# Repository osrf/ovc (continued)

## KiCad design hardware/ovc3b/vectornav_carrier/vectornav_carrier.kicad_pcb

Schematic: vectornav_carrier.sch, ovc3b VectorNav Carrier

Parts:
C14, C16, C21, C24, C25: 100n; C_0603_1608Metric; MPN CL10B104KO8NNNC
C20, C22: 47p; C_0603_1608Metric; MPN GCM1885C2A470JA16D
C23: 10u; C_0603_1608Metric; MPN GRM188R61A106KE69D
D1: RXLED; LED_0603_1608Metric; MPN LTST-C191KRKT
D2: TXLED; LED_0603_1608Metric; MPN LTST-C191KGKT
FB1: ferrite; R_0603_1608Metric; MPN BLM18KG601SN1D
H1, H2, H3, H4: MountingHole_Pad; MountingHole_2.2mm_M2_Pad
J1: camera; PinSocket_2x08_P2.00mm_Vertical
J2: Xilinx programmer; PinHeader_2x07_P2.00mm_Vertical_SMD; MPN 0878321420
J3: ROOT CONSOLE; PinHeader_1x03_P2.54mm_Vertical; MPN DNP
J4: VECTORNAV_UART; PinHeader_1x03_P2.54mm_Vertical; MPN DNP
J5: USB_B_Micro; USB_Micro-B_Wuerth_629105150521_CircularHoles; MPN 629105150521
R1, R2: 27R; R_0603_1608Metric; MPN RC0603FR-0727RL
R3, R4: 270R; R_0603_1608Metric; MPN RC0603FR-07270RL
U1: VN-100; MPN DNP
U5: SN74AXCH8T245; TSSOP-24_4.4x7.8mm_P0.65mm; MPN SN74AXCH8T245PWR
U8: FT230XS; SSOP-16_3.9x4.9mm_P0.635mm; MPN FT230XS-R

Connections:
+1V2: C14.1, J1.4, U5.1 (VCCA), U5.2 (DIR1), U5.11 (DIR2)
/AUX0_1V2: J1.3, U5.8 (A6)
/AUX1_1V2: J1.5, U5.5 (A3)
/AUX2_1V2: J1.7, U5.4 (A2)
/AUX3_1V2: J1.9, U5.3 (A1)
/AUX4_1V2: J1.11, U5.7 (A5)
/AUX5_1V2: J1.6, U5.6 (A4)
/IMU_CS: U1.23 (SPI_CS#), U5.18 (B4)
/IMU_MISO: U1.19 (SPI_MISO), U5.16 (B6)
/IMU_MOSI: U1.17 (SPI_MOSI), U5.20 (B2)
/IMU_NRST: U1.21 (NRST), U5.19 (B3)
/IMU_RX1: J4.2, U1.13 (RX1)
/IMU_RX2: U1.6 (RX2)
/IMU_SCK: U1.16 (SPI_SCK), U5.21 (B1)
/IMU_SYNC_OUT: U1.9 (SYNC_OUT), U5.17 (B5)
/IMU_TX1: J4.3, U1.12 (TX1)
/IMU_TX2: U1.5 (TX2)
/JTAG_TCK: J1.14, J2.6
/JTAG_TDI: J1.12, J2.10
/JTAG_TDO: J1.13, J2.8
/JTAG_TMS: J1.15, J2.4
/ROOT_RX: J1.10, J3.2, U8.1 (TXD)
/ROOT_TX: J1.8, J3.3, U8.4 (RXD)
/RXLED: R3.2, U8.14 (CBUS1)
/TXLED: R4.2, U8.7 (CBUS2)
/USB_3V3: C25.1, D1.2 (A), D2.2 (A), U8.3 (VCCIO), U8.10 (3V3OUT), U8.11 (~RESET)
/USB_D+: R1.1, U8.8 (USBDP)
/USB_D-: R2.1, U8.9 (USBDM)
/USB_VCC: C23.1, C24.1, FB1.1, U8.12 (VCC)
/VCC_JTAG: J1.16, J2.2
GND: C14.2, C16.2, C20.2, C21.2, C22.2, C23.2, C24.2, C25.2, H1.1, H2.1, H3.1, H4.1, J1.2, J2.3, J2.5, J2.7, J2.9, J2.11, J2.13, J3.1, J4.1, J5.5 (GND), U1.1 (GND), U1.2 (GND), U1.3 (GND), U1.4 (GND), U1.18 (GND), U1.28 (GND), U1.30 (GND), U5.12 (GND), U5.13 (GND), U5.14 (B8), U5.15 (B7), U5.22 (~OE), U8.5 (GND), U8.13 (GND)
unnamed: C20.1, J5.3 (D+), R1.2
unnamed: C21.1, FB1.2, J5.1 (VBUS)
unnamed: C22.1, J5.2 (D-), R2.2
unnamed: D1.1 (K), R3.1
unnamed: D2.1 (K), R4.1

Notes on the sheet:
VN-100
always enabled 1:4 A->B 5:8 B->A
INPUT
OUTPUT
USB-UART for linux root console

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
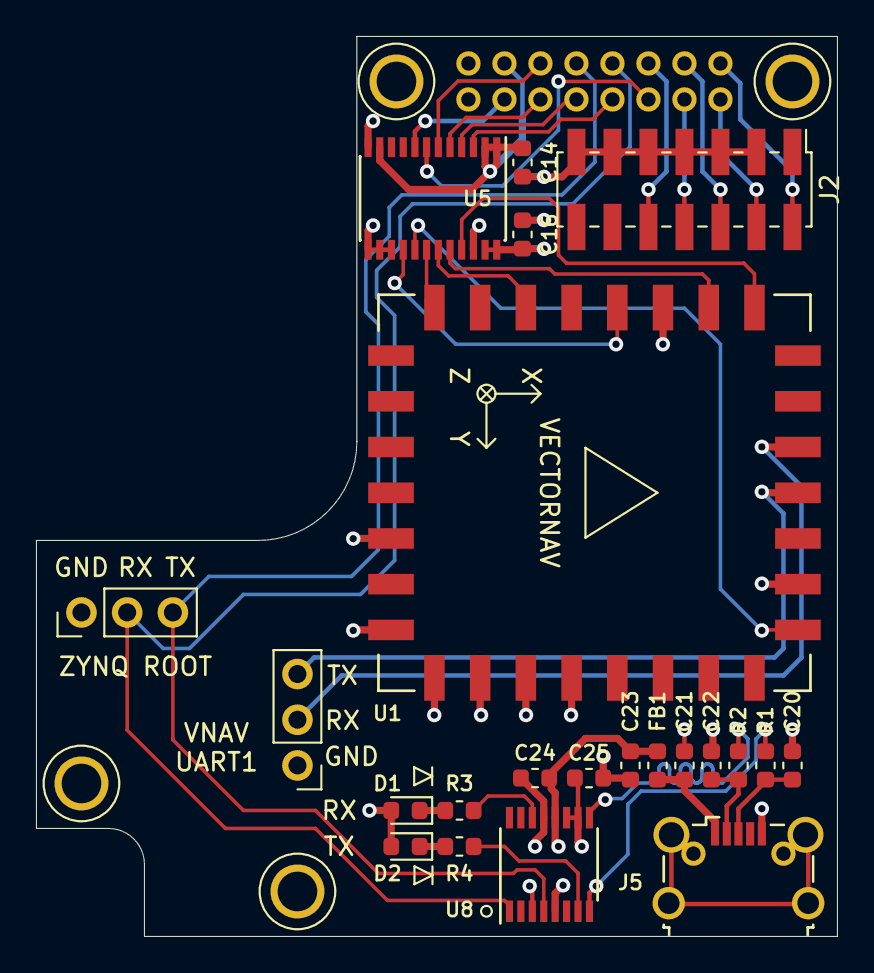
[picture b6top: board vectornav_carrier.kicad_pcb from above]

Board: 4 copper layers, 44.5 x 50.0 mm, 27 parts (1 on the bottom side), 35 nets.

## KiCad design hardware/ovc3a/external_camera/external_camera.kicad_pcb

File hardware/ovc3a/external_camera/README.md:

# Lens holders
Lens holders have 20mm spacing. There are various options that work fine.
We have used PT-LH010M from m12lenses.com with good results:
https://www.m12lenses.com/CNC-Machined-M12-Lens-Holder-Metal-p/pt-lh010m.htm

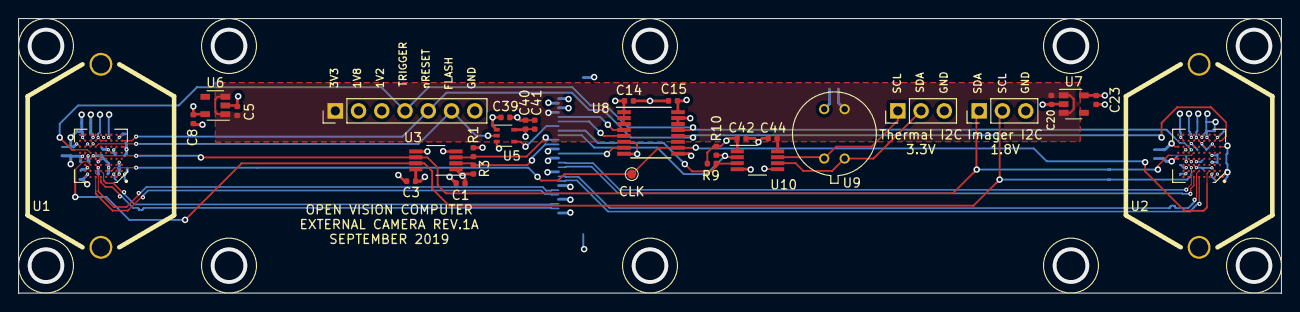
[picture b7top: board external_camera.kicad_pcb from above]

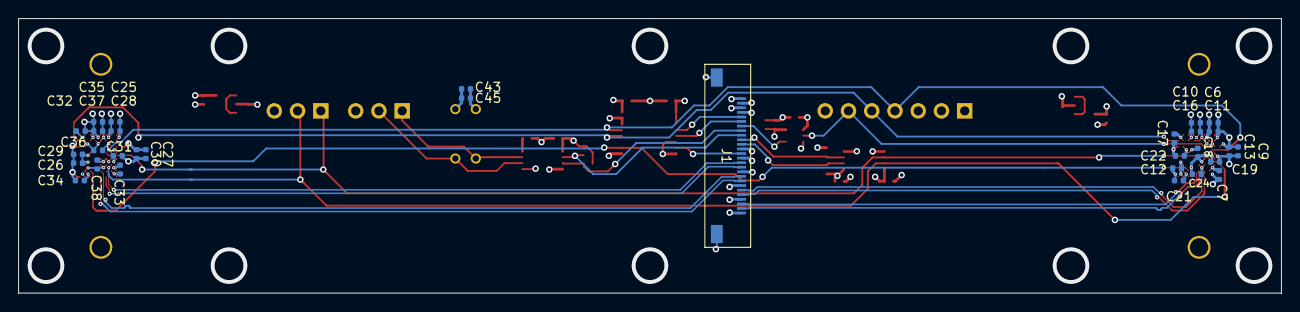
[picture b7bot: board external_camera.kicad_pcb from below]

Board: 6 copper layers, 138.0 x 30.0 mm, 63 parts (31 on the bottom side), 30 nets.

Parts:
C1, C3, C11, C12, C13, C14, C15, C16, C17, C18, C19, C21, C22, C24, C28, C29, C30, C32, C33, C34, C35, C36, C37, C38, C39, C40, C42, C43, C44: 100n; C_0402_1005Metric
C5, C8, C20, C23, C45: 1u; C_0402_1005Metric
C6, C7, C9, C10, C25, C26, C27, C31, C41: 10u; C_0402_1005Metric
J1: FFC; MOLEX_505110_2691
J2, J3: DNP; LENS_HOLDER_20MM_PT-LH010M
J4: DNP; PinHeader_1x07_P2.54mm_Vertical
J5, J6: DNP; PinHeader_1x03_P2.54mm_Vertical
R1, R3: 2k2; R_0402_1005Metric
R9, R10: DNP; R_0402_1005Metric
TP1: DNP; TestPoint_Pad_D1.0mm
U1, U2: AR0144CS; BGA-72_9x8_5.545x5.565mm
U3, U10: TCA9803; VSSOP-8_3.0x3.0mm_P0.65mm
U5: SN74AUP1T34DCK; SOT-353_SC-70-5
U6, U7: LP5907MFX-2.8; SOT-23-5
U8: SN74AXC4T245PWR; TSSOP-16_4.4x5mm_P0.65mm
U9: DNP; Melexis_TO-39

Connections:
+1V2: C1.1, C10.1, C14.1, C16.1, C19.1, C21.1, C22.1, C24.1, C31.1, C34.1, C35.1, C36.1, C37.1, C38.1, C40.1, C41.1, C42.1, J1.2, J4.3, R1.1, R3.1, R9.1, R10.1, U1.A3, U1.B2, U1.C5, U1.C6, U1.D8, U1.F2, U1.G4, U1.G5, U1.G6, U2.A3, U2.B2, U2.C5, U2.C6, U2.D8, U2.F2, U2.G4, U2.G5, U2.G6, U3.1, U3.5, U5.5, U8.1, U8.2, U8.3, U10.1, U10.5
+1V8: C3.1, C7.1, C12.1, C15.1, C18.1, C26.1, C29.1, C33.1, C39.1, J1.3, J4.2, U1.A2, U1.B7, U1.B8, U1.C2, U1.C8, U1.E3, U2.A2, U2.B8, U2.C2, U2.C8, U2.E3, U3.8, U5.1, U8.16
+3V3: C5.1, C20.1, C43.1, C44.1, C45.1, J1.4, J4.1, U6.1, U6.3, U7.1, U7.3, U9.2, U10.8
/CAM0_2V8: C6.1, C8.1, C9.1, C11.1, C13.1, C17.1, U1.F9, U1.G2, U1.G8, U1.H1, U1.H2, U1.H8, U1.H9, U6.5
/CAM1_2V8: C23.1, C25.1, C27.1, C28.1, C30.1, C32.1, U2.F9, U2.G2, U2.G8, U2.H1, U2.H2, U2.H8, U2.H9, U7.5
/EXTCLK_1V2: J1.13, U8.7
/EXTCLK_1V8: TP1.1, U1.B3, U2.B3, U8.10
/FLASH_1V2: J1.7, U5.4
/FLASH_1V8: J4.6, U1.F6, U5.2
/MIPI_CLK0+: J1.25, U1.A5
/MIPI_CLK0-: J1.24, U1.B5
/MIPI_CLK1+: J1.19, U2.A5
/MIPI_CLK1-: J1.18, U2.B5
/MIPI_DAT0+: J1.22, U1.A6
/MIPI_DAT0-: J1.21, U1.B6
/MIPI_DAT1+: J1.16, U2.A6
/MIPI_DAT1-: J1.15, U2.B6
/RESET_1V2: J1.6, U8.5
/RESET_1V8: J4.5, U1.G1, U2.G1, U8.12
/SCL0_1V2: J1.11, R3.2, U3.2
/SCL0_1V8: J5.2, U1.C7, U2.C7, U3.7
/SCL1_1V2: J1.9, R10.2, U10.2
/SCL1_3V3: J6.1, U9.4, U10.7
/SDA0_1V2: J1.10, R1.2, U3.3
/SDA0_1V8: J5.1, U1.E6, U2.E6, U3.6
/SDA1_1V2: J1.8, R9.2, U10.3
/SDA1_3V3: J6.2, U9.1, U10.6
/TRIGGER_1V2: J1.5, U8.4
/TRIGGER_1V8: J4.4, U1.E7, U2.E7, U8.13
GND: C1.2, C3.2, C5.2, C6.2, C7.2, C8.2, C9.2, C10.2, C11.2, C12.2, C13.2, C14.2, C15.2, C16.2, C17.2, C18.2, C19.2, C20.2, C21.2, C22.2, C23.2, C24.2, C25.2, C26.2, C27.2, C28.2, C29.2, C30.2, C31.2, C32.2, C33.2, C34.2, C35.2, C36.2, C37.2, C38.2, C39.2, C40.2, C41.2, C42.2, C43.2, C44.2, C45.2, J1.1, J1.12, J1.14, J1.17, J1.20, J1.23, J1.26, J1.27, J2.1, J3.1, J4.7, J5.3, J6.3, U1.A1, U1.A8, U1.D5, U1.D6, U1.D7, U1.D9, U1.E8, U1.F1, U1.F7, U1.F8, U1.G3, U1.G7, U1.H3, U1.H4, U1.H5, U1.H6, U1.H7, U2.A1, U2.A8, U2.B7, U2.D5, U2.D6, U2.D7, U2.D9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

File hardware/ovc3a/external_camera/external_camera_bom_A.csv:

Component,Quantity Per PCB,References,Value,Footprint,MFN,MPN,D1N,D1PN
1,29,C1 C3 C11 C12 C13 C14 C15 C16 C17 C18 C19 C21 C22 C24 C28 C29 C30 C32 C33 C34 C35 C36 C37 C38 C39 C40 C42 C43 C44,100n,C_0402_1005Metric,Samsung,CL05F104ZO5NNNC,Digikey,1276-1004-1-ND
2,9,C6 C7 C9 C10 C25 C26 C27 C31 C41,10u,C_0402_1005Metric,Samsung,CL05A106MP8NUB8,Digikey,1276-6830-1-ND
3,5,C5 C8 C20 C23 C45,1u,C_0402_1005Metric,Samsung,CL05A105KA5NQNC,Digikey,1276-1445-1-ND
4,2 (DNF),J2 J3,DNP,LENS_HOLDER_20MM_PT-LH010M,DNP,DNP,DNP,DNP
5,1 (DNF),J4,DNP,PinHeader_1x07_P2.54mm_Vertical,DNP,DNP,DNP,DNP
6,2 (DNF),J5 J6,DNP,PinHeader_1x03_P2.54mm_Vertical,DNP,DNP,DNP,DNP
7,1,J1,FFC,MOLEX_505110_2691,Molex,5051102691,Digikey,WM24281CT-ND
8,4,R1 R3 R9 R10,2k2,R_0402_1005Metric,Yageo,RC0402FR-072K2L,Digikey,311-2.20KLRCT-ND
9,2,U1 U2,AR0144CS,BGA-72_9x8_5.545x5.565mm,ON Semiconductor,AR0144CSSC00SUKA0-CPBR2,Digikey,AR0144CSSC00SUKA0-CPBR2OS-ND
10,1 (DNF),U9,DNP,Melexis_TO-39,DNP,DNP,DNP,DNP
11,2,U6 U7,LP5907MFX-2.8,SOT-23-5,Texas Instruments,LP5907MFX-2.8/NOPB,Digikey,296-39063-1-ND
12,1,U5,SN74AUP1T34DCK,SOT-353_SC-70-5,Texas Instruments,SN74AUP1T34DCKR,Digikey,296-34900-1-ND
13,1,U8,SN74AXC4T245PWR,TSSOP-16_4.4x5mm_P0.65mm,Texas Instruments,SN74AXC4T245PWR,Digikey,296-53472-1-ND
14,2,U3 U10,TCA9803,VSSOP-8_3.0x3.0mm_P0.65mm,Texas Instruments,TCA9803DGKR,Digikey,296-47829-1-ND





Component Groups:,14
Component Count:,62
Fitted Components:,56
Number of PCBs:,1
Total components:,56
Schematic Version:,A
Schematic Date:,2019-07-10
PCB Variant:,['default']
BoM Date:,Mon 23 Sep 2019 04:11:05 PM +08
Schematic Source:,/home/luca/hw/ovc/hardware/ovc3a/external_camera/external_camera.sch
KiCad Version:,Eeschema 5.99.0-unknown-bba949c~100~ubuntu18.04.1

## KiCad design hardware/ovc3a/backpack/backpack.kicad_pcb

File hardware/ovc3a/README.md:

# ovc3 early design concept

The idea for OVC3 is to dramatically reduce costs from OVC2 by using a
mass-produced high-density module for the FPGA/SoC, RAM, and so on. Ideally
this module will contain a Zynq UltraScale+ SoC with I/O that can function as a
USB3 transceiver.

Some candidate modules:
 * Trenz TE0820 (40mm x 50mm)
 * Trenz TE0803 / TE0808 (52mm x 76mm)
 * UltraZed
 * Enclustra Mercury

# Board Stack

For the smallest front cross-sectional area, it would be necessary to keep
the "sensor" and "compute" portions on separate boards. Unfortunately, this
would also increase small-quantity production costs.

Placing the compute module on the sensor board would make it larger/uglier,
but also keep costs down.

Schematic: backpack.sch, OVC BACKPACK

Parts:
C1, C4, C5, C8, C23: 10u; C_0603_1608Metric
C2, C3, C6, C7, C9, C10, C11, C12, C13, C14, C15, C16, C17, C18, C19, C21, C24, C25, C26: 100n; C_0603_1608Metric
C20, C22: 47p; C_0603_1608Metric
D1: RXLED; LED_0603_1608Metric
D2: TXLED; LED_0603_1608Metric
FB1, FB2: ferrite; R_0603_1608Metric
H1, H2, H3, H4, H5, H6, H7, H8: MountingHole_Pad; MountingHole_3.2mm_M3_DIN965_Pad
J1: GPIO1; Molex_Nano-Fit_105313-xx05_1x05_P2.50mm_Horizontal
J2: TO_CAMERA; PinHeader_2x15_P1.27mm_Vertical
J3: ROOT CONSOLE; PinHeader_1x03_P2.54mm_Vertical
J4: RS232; Molex_Nano-Fit_105313-xx03_1x03_P2.50mm_Horizontal
J5: USB_B_Micro; USB_Micro-B_Wuerth_629105150521_CircularHoles
J6: IMU_UART2; PinHeader_1x03_P2.54mm_Vertical
J7: IMU_UART0; PinHeader_1x03_P2.54mm_Vertical
J8: debug; PinHeader_2x05_P2.54mm_Vertical
J9: debug; PinHeader_1x03_P2.54mm_Vertical
R1, R2: 27R; R_0603_1608Metric
R3, R4: 270R; R_0603_1608Metric
R5, R6: 10k; R_0603_1608Metric
U1: VN-100
U2, U3: ISOW7842; SOIC-16W_7.5x10.3mm_P1.27mm
U4: MAX3221E; TSSOP-16_4.4x5mm_P0.65mm
U5, U6: SN74AXCH8T245; TSSOP-24_4.4x7.8mm_P0.65mm
U7: SN74AVCH2T45; VSSOP-8_2.3x2mm_P0.5mm
U8: FT230XS; SSOP-16_3.9x4.9mm_P0.635mm
U9: uIMU-2

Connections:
+1V2: J2.11, J2.13
+1V8: C14.1, C15.1, C18.1, J2.1, J2.2, U5.1 (VCCA), U5.2 (DIR1), U5.11 (DIR2), U6.1 (VCCA), U6.2 (DIR1), U6.11 (DIR2), U7.1, U7.5
/BONUS_INPUT: J8.3, U6.16 (B6)
/GPIO0_1V8: J2.4, U5.10 (A8)
/GPIO1A: U2.3 (INA), U5.19 (B3)
/GPIO1A_ISO: J1.1, U2.14 (OUTA)
/GPIO1B: U2.4 (INB), U5.18 (B4)
/GPIO1B_ISO: J1.2, U2.13 (OUTB)
/GPIO1C: U2.5 (OUTC), U5.17 (B5)
/GPIO1C_ISO: J1.3, R5.1, U2.12 (INC)
/GPIO1D: U2.6 (OUTD), U5.16 (B6)
/GPIO1D_ISO: J1.4, R6.1, U2.11 (IND)
/GPIO1_1V8: J2.6, U5.9 (A7)
/GPIO1_GND_ISO: C3.2, C4.2, J1.5, R5.2, R6.2, U2.9 (GND2), U2.10 (EN2), U2.15 (GND2)
/GPIO1_VCC_ISO: C3.1, C4.1, U2.16 (VCC2)
/GPIO2_1V8: J2.8, U5.8 (A6)
/GPIO3_1V8: J2.10, U5.7 (A5)
/GPIO4_1V8: J2.12, U5.6 (A4)
/GPIO5_1V8: J2.14, U5.5 (A3)
/GPIO6_1V8: J2.16, U5.4 (A2)
/GPIO7_1V8: J2.18, U5.3 (A1)
/GPIO8_1V8: J2.21, U6.3 (A1)
/GPIO9_1V8: J2.23, U6.4 (A2)
/GPIO10_1V8: J2.25, U6.5 (A3)
/GPIO11_1V8: J2.27, U6.6 (A4)
/GPIO12_1V8: J2.26, U6.7 (A5)
/GPIO13_1V8: J2.24, U6.8 (A6)
/GPIO14_1V8: J2.22, U6.9 (A7)
/GPIO15_1V8: J2.20, U6.10 (A8)
/GPIO16_1V8: J2.17, U7.2
/GPIO17_1V8: J2.19, U7.3
/IMU_CS: J9.2, U1.23 (SPI_CS#), U7.6, U9.8
/IMU_MISO: J8.4, U1.19 (SPI_MISO), U6.15 (B7), U9.7
/IMU_MOSI: J8.7, U1.17 (SPI_MOSI), U6.20 (B2), U9.6
/IMU_NRST: J8.10, U1.21 (NRST), U6.21 (B1), U9.12
/IMU_RX0: J7.2, U9.18
/IMU_RX1: J8.5, U1.13 (RX1), U6.18 (B4)
/IMU_RX2: J6.2, U1.6 (RX2)
/IMU_SCK: J8.8, U1.16 (SPI_SCK), U6.19 (B3), U9.9
/IMU_SYNC_IN: J9.1, U1.22 (SYNC_IN), U7.7, U9.5
/IMU_SYNC_OUT: J8.2, U1.9 (SYNC_OUT), U6.14 (B8), U9.20
/IMU_TX0: J7.1, U9.19
/IMU_TX1: J8.6, U1.12 (TX1), U6.17 (B5)
/IMU_TX2: J6.1, U1.5 (TX2)
/ISO_GND_RS232: C7.2, C8.2, C11.2, C12.1, C13.1, J4.3, U3.9 (GND2), U3.10 (EN2), U3.15 (GND2), U4.1 (~EN), U4.14 (GND)
/ISO_RS232_DIN: U3.14 (OUTA), U4.11 (DIN)
/ISO_RS232_DOUT: J4.1, U4.13 (DOUT)
/ISO_RS232_FORCEON: U3.13 (OUTB), U4.12 (FORCEON)
/ISO_RS232_INVALID: U3.11 (IND), U4.10 (~INVALID)
/ISO_RS232_RIN: J4.2, U4.8 (RIN)
/ISO_RS232_ROUT: U3.12 (INC), U4.9 (ROUT)
/ISO_VCC_RS232: C7.1, C8.1, C11.1, U3.16 (VCC2), U4.15 (VCC), U4.16 (~FORCEOFF)
/ROOT_RX: J2.28, J3.1, U8.1
/ROOT_TX: J2.30, J3.2, U8.4
/RS232_DIN: U3.3 (INA), U5.21 (B1)
/RS232_FORCEON: U3.4 (INB), U5.20 (B2)
/RS232_INVALID: U3.6 (OUTD), U5.14 (B8)
/RS232_ROUT: U3.5 (OUTC), U5.15 (B7)
/RXLED: R3.2, U8.14
/TXLED: R4.2, U8.7
/USB_3V3: C25.1, D1.2, D2.2, U8.3, U8.10, U8.11
/USB_DM: R2.1, U8.9
/USB_DP: R1.1, U8.8
/USB_VCC: C23.1, C24.1, FB1.1, U8.12
GND: C1.2, C2.2, C5.2, C6.2, C14.2, C15.2, C16.2, C17.2, C18.2, C19.2, C20.2, C21.2, C22.2, C23.2, C24.2, C25.2, C26.2, J2.3, J2.9, J2.15, J2.29, J3.3, J5.5, J6.3, J7.3, J8.9, J9.3, U1.1 (GND), U1.2 (GND), U1.3 (GND), U1.4 (GND), U1.18 (GND), U1.28 (GND), U1.30 (GND), U2.2 (GND1), U2.8 (GND1), U3.2 (GND1), U3.8 (GND1), U5.12 (GND), U5.13 (GND), U5.22 (~OE), U6.12 (GND), U6.13 (GND), U6.22 (~OE), U7.4, U8.5, U8.13, U9.10, U9.11, U9.21
unnamed: C9.1, U4.2 (C1+)
unnamed: C9.2, U4.4 (C1-)
unnamed: C10.1, U4.5 (C2+)
unnamed: C10.2, U4.6 (C2-)
unnamed: C12.2, U4.3 (V+)
unnamed: C13.2, U4.7 (V-)
unnamed: C20.1, J5.3, R1.2
unnamed: C21.1, FB1.2, J5.1
unnamed: C22.1, J5.2, R2.2
unnamed: C26.1, FB2.2, U9.3, U9.22
unnamed: D1.1, R3.1
unnamed: D2.1, R4.1

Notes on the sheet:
MOUNTING HOLES
TRENZ MOUNTING HOLES
V_ISO set to 3v3
Isolator for RS-232
always enabled 1:4 A->B 5:8 B->A
Isolator for GPIO
RS-232
VN-100
OUTPUT
INPUT
A->B
InertialSense uIMU family
USB-UART for linux root console
input pulldowns

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
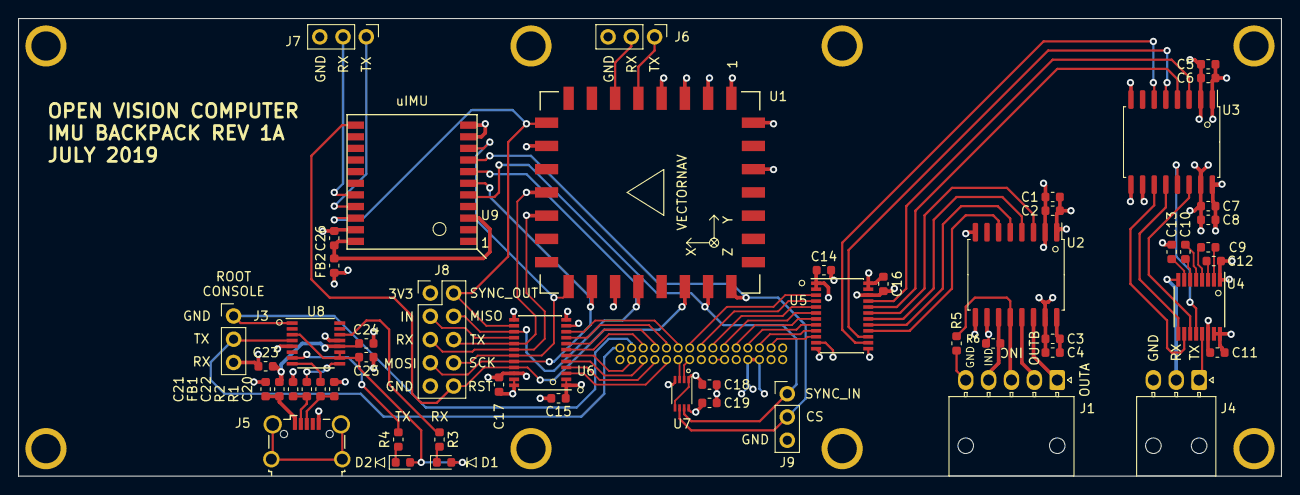
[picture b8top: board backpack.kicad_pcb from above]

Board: 4 copper layers, 138.0 x 50.0 mm, 62 parts (1 on the bottom side), 78 nets.

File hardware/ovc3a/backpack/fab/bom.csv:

# Bill of Materials for 'OVC BACKPACK' rev.A
# Schematic date: Mon Jul  8 23:24:45 2019
Line Item,Quantity,Designator,Footprint,Value,Manufacturer,Manufacturer Part Number
1,5,"C1,C4,C5,C8,C23",Capacitor_SMD:C_0603_1608Metric,10u,Murata,GRM188R61A106KE69D
2,19,"C2,C3,C6,C7,C9,C10,C11,C12,C13,C14,C15,C16,C17,C18,C19,C21,C24,C25,C26",Capacitor_SMD:C_0603_1608Metric,100n,Samsung,CL10B104KO8NNNC
3,2,"C20,C22",Capacitor_SMD:C_0603_1608Metric,47p,Murata,GCM1885C2A470JA16D
4,1,"D1",LED_SMD:LED_0603_1608Metric,RXLED,Lite-On,LTST-C191KRKT
5,1,"D2",LED_SMD:LED_0603_1608Metric,TXLED,Lite-On,LTST-C191KGKT
6,2,"FB1,FB2",Resistor_SMD:R_0603_1608Metric,ferrite,Murata,BLM18KG601SN1D
7,1,"J1",Connector_Molex:Molex_Nano-Fit_105313-xx05_1x05_P2.50mm_Horizontal,GPIO1,Molex,WM15144-ND
8,1,"J2",Connector_PinHeader_1.27mm:PinHeader_2x15_P1.27mm_Vertical,TO_CAMERA,Amphenol/FCI,20021111-00030T4LF
9,5,"J3,J6,J7,J8,J9",DNP,DNP,DNP,DNP
10,1,"J4",Connector_Molex:Molex_Nano-Fit_105313-xx03_1x03_P2.50mm_Horizontal,RS232,Molex,WM15142-ND
11,1,"J5",Connector_USB:USB_Micro-B_Wuerth_629105150521_CircularHoles,USB_B_Micro,Wurth,629105150521
12,2,"R1,R2",Resistor_SMD:R_0603_1608Metric,27R,Yageo,RC0603FR-0727RL
13,2,"R3,R4",Resistor_SMD:R_0603_1608Metric,270R,Yageo,RC0603FR-07270RL
14,2,"R5,R6",Resistor_SMD:R_0603_1608Metric,10k,Yageo,RC0603FR-0710KL
15,2,"U1,U9",DNP,DNP,DNP,DNP
16,2,"U2,U3",Package_SO:SOIC-16W_7.5x10.3mm_P1.27mm,ISOW7842,Texas Instruments,ISOW7842DWER
17,1,"U4",Package_SO:TSSOP-16_4.4x5mm_P0.65mm,MAX3221E,Texas Instruments,MAX3221EIPWR
18,2,"U5,U6",Package_SO:TSSOP-24_4.4x7.8mm_P0.65mm,SN74AXCH8T245,Texas Instruments,SN74AXCH8T245PWR
19,1,"U7",Package_SO:VSSOP-8_2.3x2mm_P0.5mm,SN74AVCH2T45,Texas Instruments,SN74AVCH2T45DCUT
20,1,"U8",Package_SO:SSOP-16_3.9x4.9mm_P0.635mm,FT230XS,FTDI,FT230XS-R

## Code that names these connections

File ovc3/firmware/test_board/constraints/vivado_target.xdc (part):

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set_property IOSTANDARD LVCMOS12 [get_ports CAM1_EXTCLK]
set_property PACKAGE_PIN B8 [get_ports CAM1_NRESET]
set_property IOSTANDARD LVCMOS12 [get_ports CAM1_NRESET]
set_property PACKAGE_PIN G5 [get_ports CAM1_SCL]
set_property IOSTANDARD LVCMOS12 [get_ports CAM1_SDA]
set_property PACKAGE_PIN C8 [get_ports {CAM1_TRIG[0]}]
set_property IOSTANDARD LVCMOS12 [get_ports {CAM1_TRIG[0]}]
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set_property IOSTANDARD LVCMOS12 [get_ports ICM_SPI_MISO]
set_property IOSTANDARD LVCMOS12 [get_ports ICM_SPI_CS]
set_property IOSTANDARD LVCMOS12 [get_ports ICM_SPI_CLK]
set_property PACKAGE_PIN AB4 [get_ports BONUS1_EXTCLK]
set_property PACKAGE_PIN AG6 [get_ports BONUS1_RESET]
set_property PACKAGE_PIN AB1 [get_ports BONUS1_SCL0]
set_property PACKAGE_PIN AC1 [get_ports BONUS1_SDA0]
set_property PACKAGE_PIN AB3 [get_ports BONUS1_TRIGGER]
set_property IOSTANDARD LVCMOS12 [get_ports BONUS1_EXTCLK]
set_property IOSTANDARD LVCMOS12 [get_ports BONUS1_FLASH]
set_property IOSTANDARD LVCMOS12 [get_ports BONUS1_RESET]
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set_property IOSTANDARD LVCMOS12 [get_ports BONUS1_SDA1]
set_property IOSTANDARD LVCMOS12 [get_ports BONUS1_TRIGGER]
set_property IOSTANDARD MIPI_DPHY_DCI [get_ports BONUS2_CLK0P]
set_property PACKAGE_PIN E3 [get_ports BONUS2_EXTCLK]
set_property PACKAGE_PIN G6 [get_ports BONUS2_FLASH]
set_property PACKAGE_PIN D9 [get_ports BONUS2_RESET]
set_property PACKAGE_PIN E4 [get_ports BONUS2_SCL0]
set_property PACKAGE_PIN F2 [get_ports BONUS2_SCL1]
set_property PACKAGE_PIN AE3 [get_ports BONUS1_SCL1]
set_property PACKAGE_PIN F6 [get_ports BONUS2_SDA1]
set_property PACKAGE_PIN E9 [get_ports BONUS2_TRIGGER]
set_property IOSTANDARD LVCMOS12 [get_ports BONUS2_EXTCLK]
set_property IOSTANDARD LVCMOS12 [get_ports BONUS2_FLASH]
set_property IOSTANDARD LVCMOS12 [get_ports BONUS2_RESET]
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set_property IOSTANDARD LVCMOS12 [get_ports BONUS2_SCL1]
set_property IOSTANDARD LVCMOS12 [get_ports BONUS2_SDA1]
set_property IOSTANDARD LVCMOS12 [get_ports BONUS2_TRIGGER]
set_property PACKAGE_PIN AB8 [get_ports BONUS3_EXTCLK]
set_property PACKAGE_PIN AF5 [get_ports BONUS3_FLASH]
set_property PACKAGE_PIN AH8 [get_ports BONUS3_RESET]
set_property PACKAGE_PIN AC8 [get_ports BONUS3_SCL0]
set_property PACKAGE_PIN AF6 [get_ports BONUS3_SCL1]
set_property PACKAGE_PIN AF7 [get_ports BONUS3_SDA0]
set_property PACKAGE_PIN AE5 [get_ports BONUS3_SDA1]
set_property PACKAGE_PIN AH7 [get_ports BONUS3_TRIGGER]
set_property IOSTANDARD LVCMOS12 [get_ports BONUS3_EXTCLK]
set_property IOSTANDARD LVCMOS12 [get_ports BONUS3_FLASH]
set_property IOSTANDARD LVCMOS12 [get_ports BONUS3_RESET]
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set_property IOSTANDARD LVCMOS12 [get_ports BONUS3_SDA1]
set_property IOSTANDARD LVCMOS12 [get_ports BONUS3_TRIGGER]

set_property PACKAGE_PIN E2 [get_ports BONUS2_SDA0]
set_property PACKAGE_PIN AF3 [get_ports BONUS1_SDA1]
set_property PACKAGE_PIN B9 [get_ports BONUS4_SCL0]
set_property PACKAGE_PIN A6 [get_ports BONUS4_SCL1]
set_property PACKAGE_PIN A7 [get_ports BONUS4_SDA0]
set_property PACKAGE_PIN A5 [get_ports BONUS4_SDA1]
set_property IOSTANDARD LVCMOS12 [get_ports BONUS4_EXTCLK]
set_property IOSTANDARD LVCMOS12 [get_ports BONUS4_FLASH]
set_property IOSTANDARD LVCMOS12 [get_ports BONUS4_RESET]
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set_property DRIVE 8 [get_ports BONUS2_SDA0]
set_property DRIVE 8 [get_ports BONUS2_SDA1]

set_property PACKAGE_PIN H9 [get_ports GPIO0]
set_property PACKAGE_PIN H8 [get_ports GPIO1]
set_property PACKAGE_PIN R8 [get_ports GPIO2]
set_property PACKAGE_PIN T8 [get_ports GPIO3]
set_property PACKAGE_PIN M6 [get_ports {GPIO4[0]}]
set_property PACKAGE_PIN L5 [get_ports {GPIO5[0]}]
set_property PACKAGE_PIN L3 [get_ports {GPIO6[0]}]
set_property PACKAGE_PIN L2 [get_ports GPIO7]
set_property PACKAGE_PIN L8 [get_ports GPIO8]
set_property PACKAGE_PIN M8 [get_ports GPIO9]
set_property PACKAGE_PIN J7 [get_ports {GPIO10[0]}]
set_property PACKAGE_PIN H7 [get_ports GPIO11]
set_property PACKAGE_PIN N8 [get_ports {GPIO12[0]}]
set_property PACKAGE_PIN N9 [get_ports {GPIO13[0]}]
set_property PACKAGE_PIN V8 [get_ports {GPIO13[1]}]
set_property PACKAGE_PIN U8 [get_ports {GPIO13[2]}]
set_property PACKAGE_PIN W8 [get_ports {GPIO13[3]}]
set_property PACKAGE_PIN Y8 [get_ports GPIO17]
set_property PACKAGE_PIN R7 [get_ports GPIO18]
set_property PACKAGE_PIN T7 [get_ports GPIO19]
set_property IOSTANDARD LVCMOS18 [get_ports GPIO0]
set_property IOSTANDARD LVCMOS18 [get_ports GPIO1]
set_property IOSTANDARD LVCMOS18 [get_ports GPIO2]
set_property IOSTANDARD LVCMOS18 [get_ports GPIO3]
set_property IOSTANDARD LVCMOS18 [get_ports {GPIO4[0]}]
set_property IOSTANDARD LVCMOS18 [get_ports {GPIO5[0]}]
set_property IOSTANDARD LVCMOS18 [get_ports {GPIO6[0]}]
set_property IOSTANDARD LVCMOS18 [get_ports GPIO7]
set_property IOSTANDARD LVCMOS18 [get_ports GPIO9]
set_property IOSTANDARD LVCMOS18 [get_ports GPIO8]
set_property IOSTANDARD LVCMOS18 [get_ports {GPIO10[0]}]
set_property IOSTANDARD LVCMOS18 [get_ports GPIO11]
set_property IOSTANDARD LVCMOS18 [get_ports {GPIO12[0]}]
set_property IOSTANDARD LVCMOS18 [get_ports {GPIO13[0]}]
set_property IOSTANDARD LVCMOS18 [get_ports {GPIO13[1]}]
set_property IOSTANDARD LVCMOS18 [get_ports {GPIO13[2]}]
set_property IOSTANDARD LVCMOS18 [get_ports {GPIO13[3]}]
set_property IOSTANDARD LVCMOS18 [get_ports GPIO17]
set_property IOSTANDARD LVCMOS18 [get_ports GPIO18]
set_property IOSTANDARD LVCMOS18 [get_ports GPIO19]


set_property PACKAGE_PIN U9 [get_ports DIP_SWITCH]
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set_property DRIVE 8 [get_ports CAM2_I2C_scl_io]
set_property DRIVE 8 [get_ports CAM2_I2C_sda_io]

set_property PACKAGE_PIN A8 [get_ports IMU_MISO]
set_property PACKAGE_PIN C2 [get_ports IMU_MOSI]
set_property PACKAGE_PIN B6 [get_ports IMU_CS]
set_property PACKAGE_PIN F3 [get_ports IMU_CLK]
set_property DRIVE 8 [get_ports IMU_CLK]
set_property DRIVE 8 [get_ports IMU_CS]
set_property DRIVE 8 [get_ports IMU_MOSI]
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
set_property PACKAGE_PIN A1 [get_ports CAM2_I2C_scl_io]

set_property PACKAGE_PIN AB6 [get_ports FRONT_AUX0]
set_property PACKAGE_PIN AC6 [get_ports FRONT_AUX1]
set_property PACKAGE_PIN AF1 [get_ports FRONT_AUX2]
set_property PACKAGE_PIN AG1 [get_ports FRONT_AUX3]
set_property PACKAGE_PIN AH6 [get_ports FRONT_AUX4]
set_property PACKAGE_PIN AD6 [get_ports FRONT_AUX5]

set_property IOSTANDARD LVCMOS12 [get_ports FRONT_AUX0]
set_property IOSTANDARD LVCMOS12 [get_ports FRONT_AUX1]
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set_property DRIVE 8 [get_ports BONUS3_I2C1_scl_io]
set_property DRIVE 8 [get_ports BONUS3_I2C1_sda_io]
set_property PACKAGE_PIN AG5 [get_ports BONUS4_I2C0_scl_io]
set_property PACKAGE_PIN B3 [get_ports BONUS4_TRIGGER]
set_property PACKAGE_PIN B5 [get_ports BONUS4_FLASH]
set_property PACKAGE_PIN AB6 [get_ports BONUS4_I2C0_sda_io]
set_property PACKAGE_PIN AC6 [get_ports BONUS4_I2C1_scl_io]
set_property PACKAGE_PIN AD6 [get_ports BONUS4_I2C1_sda_io]
set_property PACKAGE_PIN C9 [get_ports BONUS4_EXTCLK]
set_property PACKAGE_PIN A3 [get_ports BONUS4_RESET]
set_property IOSTANDARD LVCMOS12 [get_ports BONUS4_I2C0_scl_io]
set_property IOSTANDARD LVCMOS12 [get_ports BONUS4_I2C0_sda_io]
set_property IOSTANDARD LVCMOS12 [get_ports BONUS4_I2C1_scl_io]
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set_property DRIVE 8 [get_ports BONUS4_I2C1_scl_io]
set_property DRIVE 8 [get_ports BONUS4_I2C1_sda_io]

set_property PACKAGE_PIN AG5 [get_ports BONUS1_FLASH]

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
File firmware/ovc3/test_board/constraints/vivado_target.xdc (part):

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set_property IOSTANDARD LVCMOS12 [get_ports CAM1_EXTCLK]
set_property PACKAGE_PIN B8 [get_ports CAM1_NRESET]
set_property IOSTANDARD LVCMOS12 [get_ports CAM1_NRESET]
set_property PACKAGE_PIN G5 [get_ports CAM1_SCL]
set_property IOSTANDARD LVCMOS12 [get_ports CAM1_SDA]
set_property PACKAGE_PIN C8 [get_ports {CAM1_TRIG[0]}]
set_property IOSTANDARD LVCMOS12 [get_ports {CAM1_TRIG[0]}]
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set_property IOSTANDARD LVCMOS12 [get_ports ICM_SPI_MISO]
set_property IOSTANDARD LVCMOS12 [get_ports ICM_SPI_CS]
set_property IOSTANDARD LVCMOS12 [get_ports ICM_SPI_CLK]
set_property PACKAGE_PIN AB4 [get_ports BONUS1_EXTCLK]
set_property PACKAGE_PIN C9 [get_ports BONUS1_RESET]
set_property PACKAGE_PIN AB1 [get_ports BONUS1_SCL0]
set_property PACKAGE_PIN AC1 [get_ports BONUS1_SDA0]
set_property PACKAGE_PIN AB3 [get_ports BONUS1_TRIGGER]
set_property IOSTANDARD LVCMOS12 [get_ports BONUS1_EXTCLK]
set_property IOSTANDARD LVCMOS12 [get_ports BONUS1_FLASH]
set_property IOSTANDARD LVCMOS12 [get_ports BONUS1_RESET]
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set_property IOSTANDARD LVCMOS12 [get_ports BONUS1_SDA1]
set_property IOSTANDARD LVCMOS12 [get_ports BONUS1_TRIGGER]
set_property IOSTANDARD MIPI_DPHY_DCI [get_ports BONUS2_CLK0P]
set_property PACKAGE_PIN E3 [get_ports BONUS2_EXTCLK]
set_property PACKAGE_PIN G6 [get_ports BONUS2_FLASH]
set_property PACKAGE_PIN D9 [get_ports BONUS2_RESET]
set_property PACKAGE_PIN E4 [get_ports BONUS2_SCL0]
set_property PACKAGE_PIN F2 [get_ports BONUS2_SCL1]
set_property PACKAGE_PIN AE3 [get_ports BONUS1_SCL1]
set_property PACKAGE_PIN F6 [get_ports BONUS2_SDA1]
set_property PACKAGE_PIN E9 [get_ports BONUS2_TRIGGER]
set_property IOSTANDARD LVCMOS12 [get_ports BONUS2_EXTCLK]
set_property IOSTANDARD LVCMOS12 [get_ports BONUS2_FLASH]
set_property IOSTANDARD LVCMOS12 [get_ports BONUS2_RESET]
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set_property IOSTANDARD LVCMOS12 [get_ports BONUS2_SCL1]
set_property IOSTANDARD LVCMOS12 [get_ports BONUS2_SDA1]
set_property IOSTANDARD LVCMOS12 [get_ports BONUS2_TRIGGER]
set_property PACKAGE_PIN AB8 [get_ports BONUS3_EXTCLK]
set_property PACKAGE_PIN AF5 [get_ports BONUS3_FLASH]
set_property PACKAGE_PIN AH8 [get_ports BONUS3_RESET]
set_property PACKAGE_PIN AC8 [get_ports BONUS3_SCL0]
set_property PACKAGE_PIN AF6 [get_ports BONUS3_SCL1]
set_property PACKAGE_PIN AF7 [get_ports BONUS3_SDA0]
set_property PACKAGE_PIN AE5 [get_ports BONUS3_SDA1]
set_property PACKAGE_PIN AH7 [get_ports BONUS3_TRIGGER]
set_property IOSTANDARD LVCMOS12 [get_ports BONUS3_EXTCLK]
set_property IOSTANDARD LVCMOS12 [get_ports BONUS3_FLASH]
set_property IOSTANDARD LVCMOS12 [get_ports BONUS3_RESET]
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set_property IOSTANDARD LVCMOS12 [get_ports BONUS3_SDA1]
set_property IOSTANDARD LVCMOS12 [get_ports BONUS3_TRIGGER]

set_property PACKAGE_PIN E2 [get_ports BONUS2_SDA0]
set_property PACKAGE_PIN AF3 [get_ports BONUS1_SDA1]
set_property PACKAGE_PIN AB6 [get_ports BONUS4_SCL0]
set_property PACKAGE_PIN AF1 [get_ports BONUS4_SCL1]
set_property PACKAGE_PIN AC6 [get_ports BONUS4_SDA0]
set_property PACKAGE_PIN AG1 [get_ports BONUS4_SDA1]
set_property IOSTANDARD LVCMOS12 [get_ports BONUS4_EXTCLK]
set_property IOSTANDARD LVCMOS12 [get_ports BONUS4_FLASH]
set_property IOSTANDARD LVCMOS12 [get_ports BONUS4_RESET]
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set_property DRIVE 8 [get_ports BONUS2_SDA0]
set_property DRIVE 8 [get_ports BONUS2_SDA1]

set_property PACKAGE_PIN H9 [get_ports GPIO0]
set_property PACKAGE_PIN H8 [get_ports GPIO1]
set_property PACKAGE_PIN R8 [get_ports GPIO2]
set_property PACKAGE_PIN T8 [get_ports GPIO3]
set_property PACKAGE_PIN M6 [get_ports {GPIO4[0]}]
set_property PACKAGE_PIN L5 [get_ports {GPIO5[0]}]
set_property PACKAGE_PIN L3 [get_ports {GPIO6[0]}]
set_property PACKAGE_PIN L2 [get_ports GPIO7]
set_property PACKAGE_PIN L8 [get_ports GPIO8]
set_property PACKAGE_PIN M8 [get_ports GPIO9]
set_property PACKAGE_PIN J7 [get_ports {GPIO10[0]}]
set_property PACKAGE_PIN H7 [get_ports GPIO11]
set_property PACKAGE_PIN N8 [get_ports {GPIO12[0]}]
set_property PACKAGE_PIN N9 [get_ports {GPIO13[0]}]
set_property PACKAGE_PIN V8 [get_ports GPIO14]
set_property PACKAGE_PIN U8 [get_ports GPIO15]
set_property PACKAGE_PIN W8 [get_ports GPIO16]
set_property PACKAGE_PIN Y8 [get_ports GPIO17]
set_property IOSTANDARD LVCMOS18 [get_ports GPIO0]
set_property IOSTANDARD LVCMOS18 [get_ports GPIO1]
set_property IOSTANDARD LVCMOS18 [get_ports GPIO2]
set_property IOSTANDARD LVCMOS18 [get_ports GPIO3]
set_property IOSTANDARD LVCMOS18 [get_ports GPIO16]
set_property IOSTANDARD LVCMOS18 [get_ports GPIO17]
set_property IOSTANDARD LVCMOS18 [get_ports {GPIO4[0]}]
set_property IOSTANDARD LVCMOS18 [get_ports {GPIO5[0]}]
set_property IOSTANDARD LVCMOS18 [get_ports {GPIO6[0]}]
set_property IOSTANDARD LVCMOS18 [get_ports GPIO7]
set_property IOSTANDARD LVCMOS18 [get_ports GPIO9]
set_property IOSTANDARD LVCMOS18 [get_ports GPIO8]
set_property IOSTANDARD LVCMOS18 [get_ports {GPIO10[0]}]
set_property IOSTANDARD LVCMOS18 [get_ports {GPIO12[0]}]
set_property IOSTANDARD LVCMOS18 [get_ports GPIO11]
set_property IOSTANDARD LVCMOS18 [get_ports {GPIO13[0]}]
set_property IOSTANDARD LVCMOS18 [get_ports GPIO14]
set_property IOSTANDARD LVCMOS18 [get_ports GPIO15]
set_property DRIVE 8 [get_ports {GPIO4[0]}]
set_property DRIVE 8 [get_ports {GPIO5[0]}]
set_property DRIVE 8 [get_ports {GPIO6[0]}]
set_property DRIVE 8 [get_ports GPIO7]
set_property DRIVE 8 [get_ports {GPIO10[0]}]
set_property DRIVE 8 [get_ports {GPIO13[0]}]
set_property DRIVE 8 [get_ports {GPIO12[0]}]
set_property DRIVE 8 [get_ports GPIO14]
set_property DRIVE 8 [get_ports GPIO15]
set_property DRIVE 8 [get_ports GPIO16]
set_property DRIVE 8 [get_ports GPIO17]

set_property PACKAGE_PIN U9 [get_ports DIP_SWITCH]
set_property IOSTANDARD LVCMOS18 [get_ports DIP_SWITCH]
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set_property DRIVE 8 [get_ports CAM2_I2C_scl_io]
set_property DRIVE 8 [get_ports CAM2_I2C_sda_io]

set_property PACKAGE_PIN A8 [get_ports IMU_MISO]
set_property PACKAGE_PIN C2 [get_ports IMU_MOSI]
set_property PACKAGE_PIN B6 [get_ports IMU_CS]
set_property PACKAGE_PIN F3 [get_ports IMU_CLK]
set_property DRIVE 8 [get_ports IMU_CLK]
set_property DRIVE 8 [get_ports IMU_CS]
set_property DRIVE 8 [get_ports IMU_MOSI]
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set_property DRIVE 8 [get_ports BONUS3_I2C1_scl_io]
set_property DRIVE 8 [get_ports BONUS3_I2C1_sda_io]
set_property PACKAGE_PIN AG5 [get_ports BONUS4_I2C0_scl_io]
set_property PACKAGE_PIN AH6 [get_ports BONUS4_TRIGGER]
set_property PACKAGE_PIN AG1 [get_ports BONUS4_FLASH]
set_property PACKAGE_PIN AB6 [get_ports BONUS4_I2C0_sda_io]
set_property PACKAGE_PIN AC6 [get_ports BONUS4_I2C1_scl_io]
set_property PACKAGE_PIN AD6 [get_ports BONUS4_I2C1_sda_io]
set_property PACKAGE_PIN AG6 [get_ports BONUS4_EXTCLK]
set_property PACKAGE_PIN AF1 [get_ports BONUS4_RESET]
set_property IOSTANDARD LVCMOS12 [get_ports BONUS4_I2C0_scl_io]
set_property IOSTANDARD LVCMOS12 [get_ports BONUS4_I2C0_sda_io]
set_property IOSTANDARD LVCMOS12 [get_ports BONUS4_I2C1_scl_io]
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set_property DRIVE 8 [get_ports BONUS4_I2C1_scl_io]
set_property DRIVE 8 [get_ports BONUS4_I2C1_sda_io]

set_property PACKAGE_PIN B9 [get_ports BONUS1_FLASH]

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
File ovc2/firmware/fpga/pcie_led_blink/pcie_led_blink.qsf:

set_global_assignment -name FAMILY "Cyclone 10 GX"
set_global_assignment -name TOP_LEVEL_ENTITY top_wrapper
set_global_assignment -name ORIGINAL_QUARTUS_VERSION 18.0.0
set_global_assignment -name PROJECT_CREATION_TIME_DATE "22:09:08  MAY 26, 2018"
set_global_assignment -name LAST_QUARTUS_VERSION "18.1.0 Pro Edition"
set_global_assignment -name PROJECT_OUTPUT_DIRECTORY output_files
set_global_assignment -name MIN_CORE_JUNCTION_TEMP 0
set_global_assignment -name MAX_CORE_JUNCTION_TEMP 100
set_global_assignment -name DEVICE 10CX220YF672E6G
set_global_assignment -name DEVICE_FILTER_PACKAGE FBGA
set_global_assignment -name DEVICE_FILTER_PIN_COUNT 672
set_global_assignment -name ERROR_CHECK_FREQUENCY_DIVISOR 4
set_global_assignment -name IP_FILE ip/platform/platform_clock_in.ip
set_global_assignment -name QSYS_FILE platform.qsys
set_global_assignment -name IP_FILE ip/platform/pcie.ip
set_global_assignment -name IP_FILE ip/platform/pio_output.ip
set_global_assignment -name IP_FILE ip/platform/pcie_clock_bridge.ip
set_global_assignment -name VERILOG_FILE wrapper.v
set_global_assignment -name POWER_AUTO_COMPUTE_TJ ON
set_global_assignment -name POWER_PRESET_COOLING_SOLUTION "23 MM HEAT SINK WITH STILL AIR"
set_global_assignment -name POWER_BOARD_THERMAL_MODEL "NONE (CONSERVATIVE)"

set_location_assignment PIN_AB8 -to pcie_perst
set_instance_assignment -name IO_STANDARD "1.8 V" -to pcie_perst -entity top_wrapper

set_location_assignment PIN_N22 -to pcie_refclk
set_location_assignment PIN_N21 -to "pcie_refclk(n)"
set_instance_assignment -name IO_STANDARD HCSL -to pcie_refclk -entity top_wrapper
set_instance_assignment -name XCVR_REFCLK_PIN_TERMINATION AC_COUPLING -to pcie_refclk
set_instance_assignment -name IO_STANDARD "HSSI DIFFERENTIAL I/O" -to pcie_tx
set_instance_assignment -name IO_STANDARD "HSSI DIFFERENTIAL I/O" -to pcie_rx
set_location_assignment PIN_T24 -to pcie_rx[0]
set_location_assignment PIN_U26 -to pcie_tx[0]
set_location_assignment PIN_P24 -to pcie_rx[1]
set_location_assignment PIN_R26 -to pcie_tx[1]
set_location_assignment PIN_M24 -to pcie_rx[2]
set_location_assignment PIN_N26 -to pcie_tx[2]
set_location_assignment PIN_K24 -to pcie_rx[3]
set_location_assignment PIN_L26 -to pcie_tx[3]
set_location_assignment PIN_M1 -to aux[0]
set_location_assignment PIN_N1 -to aux[1]
#set_location_assignment PIN_T22 -to aux[2]
#set_location_assignment PIN_J21 -to aux[3]
#set_location_assignment PIN_G22 -to aux[4]
#set_location_assignment PIN_G21 -to aux[5]
#set_location_assignment PIN_D22 -to aux[6]
#set_location_assignment PIN_E21 -to aux[7]

set_location_assignment PIN_AC13 -to clk100
set_global_assignment -name AUTO_RESERVE_CLKUSR_FOR_CALIBRATION OFF

set_location_assignment PIN_E21 -to cam_clk[0]
#set_location_assignment PIN_AB15 -to "cam_clk[0](n)"
set_location_assignment PIN_C17 -to cam_dclk[0]
set_location_assignment PIN_C16 -to "cam_dclk[0](n)"
set_location_assignment PIN_C11 -to cam_sync[0]
set_location_assignment PIN_C12 -to "cam_sync[0](n)"
set_location_assignment PIN_C21 -to cam_dout[0]
set_location_assignment PIN_C20 -to "cam_dout[0](n)"
set_location_assignment PIN_D19 -to cam_dout[1]
set_location_assignment PIN_E19 -to "cam_dout[1](n)"
set_location_assignment PIN_B15 -to cam_dout[2]
set_location_assignment PIN_B13 -to cam_dout[3]
set_location_assignment PIN_C7 -to cam_rst[0]
set_location_assignment PIN_D7 -to cam_cs[0]
set_location_assignment PIN_E9 -to cam_sck[0]
set_location_assignment PIN_D8 -to cam_mosi[0]
set_location_assignment PIN_G3 -to cam_miso[0]
set_location_assignment PIN_D4 -to cam_trigger[0]

set_location_assignment PIN_AF11 -to cam_clk[1]
set_location_assignment PIN_AF19 -to cam_dclk[1]
set_location_assignment PIN_AF14 -to cam_sync[1]
set_location_assignment PIN_AF18 -to cam_dout[4]
set_location_assignment PIN_AF16 -to cam_dout[5]
set_location_assignment PIN_AE17 -to cam_dout[6]
set_location_assignment PIN_AD14 -to cam_dout[7]
set_location_assignment PIN_AF7 -to cam_rst[1]
set_location_assignment PIN_AE7 -to cam_cs[1]
set_location_assignment PIN_AE6 -to cam_sck[1]
set_location_assignment PIN_AF6 -to cam_mosi[1]
set_location_assignment PIN_AD8 -to cam_miso[1]
set_location_assignment PIN_AF8 -to cam_trigger[1]

set_location_assignment PIN_C3 -to imu_rst
set_location_assignment PIN_C6 -to imu_cs
set_location_assignment PIN_E5 -to imu_sck
set_location_assignment PIN_F4 -to imu_miso
set_location_assignment PIN_D5 -to imu_mosi
set_location_assignment PIN_E4 -to imu_sync_in
set_location_assignment PIN_H2 -to imu_sync_out

set_location_assignment PIN_D3 -to led_ci
set_location_assignment PIN_D2 -to led_di
set_instance_assignment -name IO_STANDARD "1.8 V" -to led_*
#set_instance_assignment -name SLEW_RATE 0 -to led[*]

set_instance_assignment -name IO_STANDARD LVDS -to cam_clk[*]
set_instance_assignment -name IO_STANDARD LVDS -to cam_dclk[*]
set_instance_assignment -name IO_STANDARD LVDS -to cam_dout[*]
set_instance_assignment -name IO_STANDARD LVDS -to cam_sync[*]
set_instance_assignment -name INPUT_TERMINATION DIFFERENTIAL -to cam_dclk[*]
set_instance_assignment -name INPUT_TERMINATION DIFFERENTIAL -to cam_dout[*]
set_instance_assignment -name INPUT_TERMINATION DIFFERENTIAL -to cam_sync[*]

#set_instance_assignment -name IO_STANDARD "2.5 V" -to aux[*]
#set_instance_assignment -name SLEW_RATE 0 -to aux[*]

set_instance_assignment -name IO_STANDARD "1.8 V" -to clk100
set_instance_assignment -name IO_STANDARD "1.8 V" -to imu_*
set_instance_assignment -name SLEW_RATE 0 -to imu_rst
set_instance_assignment -name SLEW_RATE 0 -to imu_cs
set_instance_assignment -name SLEW_RATE 0 -to imu_sck
set_instance_assignment -name SLEW_RATE 0 -to imu_mosi

set_instance_assignment -name IO_STANDARD "1.8 V" -to cam_rst[*]
set_instance_assignment -name SLEW_RATE 0 -to cam_rst[*]
set_instance_assignment -name IO_STANDARD "1.8 V" -to cam_cs[*]
set_instance_assignment -name SLEW_RATE 0 -to cam_cs[*]
set_instance_assignment -name IO_STANDARD "1.8 V" -to cam_sck[*]
set_instance_assignment -name SLEW_RATE 0 -to cam_sck[*]
set_instance_assignment -name IO_STANDARD "1.8 V" -to cam_mosi[*]
set_instance_assignment -name SLEW_RATE 0 -to cam_mosi[*]
set_instance_assignment -name IO_STANDARD "1.8 V" -to cam_miso[*]
set_instance_assignment -name SLEW_RATE 0 -to cam_miso[*]
set_instance_assignment -name IO_STANDARD "1.8 V" -to cam_trigger[*]
set_instance_assignment -name SLEW_RATE 0 -to cam_trigger[*]

#set_global_assignment -name ENABLE_OCT_DONE OFF
#set_global_assignment -name ENABLE_AUTONOMOUS_PCIE_HIP OFF
#set_global_assignment -name ENABLE_CONFIGURATION_PINS OFF
#set_global_assignment -name ENABLE_BOOT_SEL_PIN OFF
#set_global_assignment -name STRATIXV_CONFIGURATION_SCHEME "PASSIVE SERIAL"
#set_global_assignment -name USE_CONFIGURATION_DEVICE OFF
#set_global_assignment -name CRC_ERROR_OPEN_DRAIN ON
#set_global_assignment -name CVP_MODE "CORE INITIALIZATION AND UPDATE"
#set_global_assignment -name ENABLE_CVP_CONFDONE ON
#set_global_assignment -name OUTPUT_IO_TIMING_NEAR_END_VMEAS "HALF VCCIO" -rise
#set_global_assignment -name OUTPUT_IO_TIMING_NEAR_END_VMEAS "HALF VCCIO" -fall
#set_global_assignment -name OUTPUT_IO_TIMING_FAR_END_VMEAS "HALF SIGNAL SWING" -rise
#set_global_assignment -name OUTPUT_IO_TIMING_FAR_END_VMEAS "HALF SIGNAL SWING" -fall
#set_global_assignment -name VCCPGM_USER_VOLTAGE 1.8V
#set_global_assignment -name VCCBAT_USER_VOLTAGE 1.8V
#set_global_assignment -name VCCE_GXBL_USER_VOLTAGE 1.03V
#set_global_assignment -name VCCE_GXBR_USER_VOLTAGE 1.03V
#set_global_assignment -name VCCL_GXBL_USER_VOLTAGE 1.03V
#set_global_assignment -name VCCL_GXBR_USER_VOLTAGE 1.03V
#set_global_assignment -name CONFIGURATION_VCCIO_LEVEL 1.8V
#set_global_assignment -name SDC_FILE ovc.sdc
#set_global_assignment -name ACTIVE_SERIAL_CLOCK FREQ_100MHZ
#set_instance_assignment -name PARTITION_HIERARCHY root_partition -to | -section_id Top

#set_global_assignment -name QIP_FILE cam_pll.qip
#set_global_assignment -name SIP_FILE cam_pll.sip
#set_global_assignment -name QIP_FILE cam_rx.qip
#set_global_assignment -name QIP_FILE ovc_qsys/synthesis/ovc_qsys.qip1


set_global_assignment -name ENABLE_CONFIGURATION_PINS OFF
set_global_assignment -name ENABLE_BOOT_SEL_PIN OFF
set_global_assignment -name STRATIXV_CONFIGURATION_SCHEME "PASSIVE SERIAL"
set_global_assignment -name USE_CONFIGURATION_DEVICE OFF
set_global_assignment -name GENERATE_RBF_FILE ON
set_global_assignment -name GENERATE_PR_RBF_FILE OFF
set_global_assignment -name CRC_ERROR_OPEN_DRAIN ON
set_global_assignment -name CONFIGURATION_VCCIO_LEVEL 1.8V
set_global_assignment -name ACTIVE_SERIAL_CLOCK FREQ_100MHZ
set_global_assignment -name AUTO_RESTART_CONFIGURATION OFF
set_global_assignment -name ON_CHIP_BITSTREAM_DECOMPRESSION ON
set_global_assignment -name DEVICE_INITIALIZATION_CLOCK INIT_INTOSC
set_global_assignment -name IP_FILE ip/platform/cam_lvds_rx.ip

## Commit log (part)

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2020-11-05 towards lowest level eth tx and fcs
2020-11-09 FCS module seems to be computing the correct values now
2020-11-09 deal with final 6-byte word
2020-11-11 ethernet frame wrapper and packet-blaster
2020-11-13 WIP udp/ip header generator
2020-11-20 WIP udp tx, seems FCS is not correct yet
2020-11-23 First prototype of stereo streaming
2020-12-04 debugging fcs 16 bit leftover
2020-12-07 simplify block diagram, add some notes
2021-02-11 Added timer for trigger lines
2021-02-15 Add camera module header
2021-02-15 Add vivado project for OVC5
2021-02-25 add arduino-based latency measurement test rig
2021-03-01 Overlap MIPI RX and USB TX to reduce latency
2021-03-01 render measured latency using matplotlib
2021-03-09 Finish main schematics, start placing
2021-03-11 Add trigger lines for latency test
2021-03-18 Added petalinux project for devkit
2021-03-18 IP dir is generated
2021-03-19 Reduce Generated Code (#38)
    * Improving organization/readability in Vivado block diagram
    * Ignore synthesis output
    * IP dir is generated
    * Everything is generated from hdl and bd file.
2021-03-22 Add parts for BOM
2021-03-25 Address review feedback
    * Increase capacitance on VBUS host lines
    * Add ferrite beads to VBUS host lines
    * Add capacitance to VBUS device line
    * Add shield RC filtering circuit on USB connectors
    * Add stitching vias to perimeter of PCB
    * Switch CAM0 and CAM3 FPGA lines for simpler routing
2021-03-29 Bump kramdown from 2.3.0 to 2.3.1 in /docs
    Bumps [kramdown](https://github.com/gettalong/kramdown) from 2.3.0 to 2.3.1.
    - [Release notes](https://github.com/gettalong/kramdown/releases)
    - [Changelog](https://github.com/gettalong/kramdown/blob/master/doc/news.page)
    - [Commits](https://github.com/gettalong/kramdown/commits)
2021-03-30 Add kicad project for OVC5 (#36)
    * Start placing components
    * Finish main schematics, start placing
    * Place and route USB and MIPI lanes
    * Finished most placing and routing
    * Finish placement and routing
    * Add parts for BOM
2021-04-01 New PPA for Kicad Nightly (#41)
2021-04-06 Uncomment function calls
2021-04-07 fix image path
2021-04-08 Install packages for ovc install
2021-04-08 Update ignores
2021-04-08 Minor adjustments
2021-04-13 Add libyaml-cpp for config file
2021-04-13 Removed stray via
2021-04-13 Fix MIPI IO bank being at wrong voltage (#45)
    * Fix MIPI IO bank being at wrong voltage
    * Removed stray via
    * Added fabrication files
2021-04-13 Move usb config to setup process as it is only run once
2021-04-13 Typo
2021-04-13 Correct path issues from cding around
2021-04-16 ROS1 driver for ovc
2021-04-20 libovc based ros drivers
2021-04-20 Draw image wrt screen width
2021-04-21 Dynamic config document
2021-04-21 Get ethernet packet definitions from libovc
2021-04-21 Adding rx packet type to device driver
2021-04-21 Fix compiler warnings and do some formatting along the way
2021-04-21 Dynamic reconfigure plumbing
2021-04-21 Print on device when receiving packets
2021-04-22 Formatting with clang-format to match style
2021-04-22 Format all code
2021-04-26 Do not bin pack arguments
2021-04-26 Correct event triggers
2021-04-27 Correct code format
2021-04-28 eMMC build and loading scripts
2021-04-28 Update final message
2021-04-28 Don't double umount and fix copy
2021-05-11 WIP Vivado project for the carrier board
2021-05-19 Bump nokogiri from 1.11.1 to 1.11.4 in /docs
    Bumps [nokogiri](https://github.com/sparklemotion/nokogiri) from 1.11.1 to 1.11.4.
    - [Release notes](https://github.com/sparklemotion/nokogiri/releases)
    - [Changelog](https://github.com/sparklemotion/nokogiri/blob/main/CHANGELOG.md)
    - [Commits](https://github.com/sparklemotion/nokogiri/compare/v1.11.1...v1.11.4)
2021-05-25 Swap 0/1 inputs
2021-05-28 eMMC Scripts (#49)
    * eMMC build and loading scripts
    * Reference note
    * Update final message
    * Ignore tmp directory containing boot images
    * Don't double umount and fix copy
    * Minor script updates
2021-06-02 dhcpd starts correctly on boot, USB gadget is hot-pluggable
2021-06-03 Update README.md with pinout of OVC3a and 3b
2021-06-04 Update zusys with new pinout
2021-06-09 uio device mem location output
2021-06-09 GPIO Driver initial code
2021-06-09 Change error handling for read/write
2021-06-09 Updated for OVC5 custom carrier board
2021-06-09 Sampling triggers
2021-06-09 Trigger before reading out next frames.
2021-06-11 Camera device number
2021-06-13 Add comments regarding GPIOs for OVC3
2021-06-13 Add instructions for PetaLinux generation
2021-06-14 Add clarification to create boot image for ovc3
2021-06-18 Single line counter selected by GPIO
2021-06-23 Configs for cam 2 and 5
2021-06-24 Fix interfaces misconfiguration
2021-07-06 OVC3B pinout (#52)
    * Pinout converted from OVC3a to OVC3b
    * Update README.md with pinout of OVC3a and 3b
    * Fixed constraints for GPIO18 and GPIO19
    * Created a root README for OVC3
    * Update zusys with new pinout
    * Improved README with steps for FSBL and PMUFW for ovc3 firmware
2021-07-07 Correct board thickness. Switched P/N of top USB connector.
2021-07-07 Ignore autosaves and correct DIP switch part number
2021-07-08 Fixed picam connector orientations
2021-07-12 Downsizing 100nF and 10nF caps to 0201s
2021-07-13 Bump addressable from 2.7.0 to 2.8.0 in /docs
    Bumps [addressable](https://github.com/sporkmonger/addressable) from 2.7.0 to 2.8.0.
    - [Release notes](https://github.com/sporkmonger/addressable/releases)
    - [Changelog](https://github.com/sporkmonger/addressable/blob/main/CHANGELOG.md)
    - [Commits](https://github.com/sporkmonger/addressable/compare/addressable-2.7.0...addressable-2.8.0)
    ---
    updated-dependencies:
2021-07-13 TCA9416 for I2C level shifters and TX Caps on USB SS lanes
2021-07-20 Transition to USB7216
2021-07-21 Oscillator selected. More passives added for configuration.
2021-07-21 Correct GPIO/QWIIC voltages (actually saved)
2021-07-23 OVC5 Carrier Firmware (#54)
    * WIP Vivado project for the carrier board
    * Swap 0/1 inputs
    * Update petalinux config
    * Update device tree
    * dhcpd starts correctly on boot, USB gadget is hot-pluggable
    * uio device mem location output
2021-07-23 Placing new connectors and routing fan controls
2021-07-23 More routing cleanup and USB Upstream placement
2021-07-24 Switch up USB configuration to match routing plan
2021-07-27 Fancy registration of drivers
2021-07-29 Swap TS5USBC41 for MAX4906EF
2021-07-30 Correcting color map keys and adding documentation.
2021-07-30 Fix string issues
2021-08-02 Remove USB Muxes, add UART TX/RX Headers
2021-08-04 All routing for data lines (save for diff pair tuning).
2021-08-05 Initial length matching for CAM2
2021-08-09 Finishing touches on enable lines
2021-08-10 Feedback from Luca: pull-ups for usb power management removed, add back CONN1/2, move big ICs to top of PCB, clean up power planes
2021-08-11 Re-route all MIPI lanes with 5/6 traces
2021-08-11 Formatting
2021-08-12 Add comment regarding compiler bug
2021-08-12 Exposure adjustment
2021-08-16 Frame rate param to host side (need to implement on device)
2021-08-17 Address Luca's comments
2021-08-17 Fix drc error
2021-08-18 Miscellaneous improvements
2021-08-18 Set ips to list of strings
2021-08-18 Format
2021-08-19 Dynamic Parameters (#61)
    * Exposure adjustment
    * Remove dynamic bit-field init
    * Update exposure configuration to use floats instead of doubles
    * Formatting
    * Frame rate param to host side (need to implement on device)
    * Device code to support frame rate
2021-08-19 Only run clang format check on PR (#63)
2021-08-20 Change out of stock parts
2021-08-20 Host-side json support
2021-08-20 Correct jsoncpp behavior
2021-08-23 Adjusting drivers to handle any number of cameras
2021-08-24 Adding clarification to the JSON format
2021-08-25 Remove unneeded flag definition
2021-08-25 Clean up for loop
2021-08-25 Fix issue with empty frames
2021-08-26 Remove sensor_name from camera conf. Add in later PR
2021-08-26 API instead of jsoncpp interface
2021-08-27 Compile error
2021-08-27 Add creative commons license to top level README (#68)
    * Update README.md
    * Update README.md
2021-08-27 Picam exposure support (working)
2021-08-28 Frame id for VNAV mag and better topic names
2021-08-31 Update OVC5 Readme
2021-08-31 OVC5 doc update (#71)
    * Update OVC5 Readme
    * Add OVC5 to website
    * Delete legacy website files
2021-09-15 Adding scripts to setup/build out the QSXP bsp
2021-09-20 28 pin FFC to 22pin Picam extended connector converter board
2021-09-22 Switched to hand-solderable LDO instead of switching regulator
2021-09-28 Initial work on bandwidth test
2021-09-29 Re-write test script in python and use -R to invert server/client
2021-09-29 Hardware README
2021-09-30 Update requirements
2021-10-01 Tidying
2021-10-05 Make a benchmark package
2021-10-06 Process payload test results
2021-10-06 Option to skip benchmarks and correction from Mb -> MB
2021-10-11 Upgrade to vivado 2021.1
2021-10-21 Update schematics to revb
2021-10-28 Camera i2c handler from OVC5 (WIP)
2021-11-03 Adjust build scripts
2021-11-03 I was defeated by an exclamation point!
2021-11-03 Wrong existence check
2021-11-10 Update config for OVC5 rev B
2021-11-11 Update website documentation
2021-11-16 Skeleton of imager assignment to multiple sockets
2021-11-17 Add second subscriber to server
2022-01-25 WIP remove spinlock
2022-02-03 Update firmware for OVC5 revision B (#78)
    * Update constraints and add smbus IIC
    * Port USB and pinout constraints, WIP device scripts update
2022-02-16 Update comment
2022-02-18 Roll back to waiting whole frame before send
2022-02-22 Add greyscale image
2022-03-10 Add MLX module
2022-03-17 Initial support for ToF frames
2022-03-19 Add deep copy to returned frames
2022-03-23 First full integration demo with AR0234 hack
2022-03-25 Fully multithreaded interrupt polling
2022-03-25 Streamline clocks, enforce dma coherency
2022-03-28 Add frame id to publisher
2022-03-28 Minor cleanup
2022-03-29 Make script executable
2022-03-29 OVC5 parallel ethernet interfaces (#82)
    * Skeleton of imager assignment to multiple sockets
    * Skeleton host driver for multiple ethernets
    * Add second client to device
    * Add second subscriber to server
    * WIP multiple ethernet interfaces streaming
    * WIP remove spinlock
2022-04-12 Bump nokogiri from 1.13.3 to 1.13.4 in /docs
    Bumps [nokogiri](https://github.com/sparklemotion/nokogiri) from 1.13.3 to 1.13.4.
    - [Release notes](https://github.com/sparklemotion/nokogiri/releases)
    - [Changelog](https://github.com/sparklemotion/nokogiri/blob/v1.13.4/CHANGELOG.md)
    - [Commits](https://github.com/sparklemotion/nokogiri/compare/v1.13.3...v1.13.4)
    ---
    updated-dependencies:
